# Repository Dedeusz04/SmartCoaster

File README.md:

# Smart Coaster - ESP8266 Beverage Temperature Monitor

An embedded system built on the **NodeMCU ESP8266** that detects cup presence, monitors beverage temperature in real time, and alerts the user when the drink has cooled to a configured target temperature.

## Key Features

- Automatic cup detection (VL6180X ToF sensor)
- Non-contact temperature monitoring (MLX90614 IR sensor) with adaptive liquid temperature estimation
- Configurable brew timer and target drinking temperature
- 128×64 OLED display with rotary encoder menu
- Persistent user settings (EEPROM)
- Audible buzzer alerts
- **Mobile Push Notifications** via [ntfy.sh](https://ntfy.sh) (Max priority alarm)
- **Wi-Fi Connectivity** with network state reporting

For a detailed description, refer to the **project report** included in this repository [v1.Raport_Bartosz.Kępa.pdf](v1.Raport_Bartosz.Kępa.pdf).

## Pin Assignment

| Function | NodeMCU Pin | GPIO |
|---|---|---|
| I2C SDA | D2 | GPIO4 |
| I2C SCL | D1 | GPIO5 |
| Encoder S1 | D5 | GPIO14 |
| Encoder S2 | D6 | GPIO12 |
| Encoder Button | D7 | GPIO13 |
| Buzzer | D0 | GPIO16 |

## Build and Flash

Requires [PlatformIO](https://platformio.org/install/ide). All library dependencies are resolved automatically.

```bash
pio run              # compile
pio run -t upload    # flash to board
pio device monitor   # serial monitor (9600 baud)
```

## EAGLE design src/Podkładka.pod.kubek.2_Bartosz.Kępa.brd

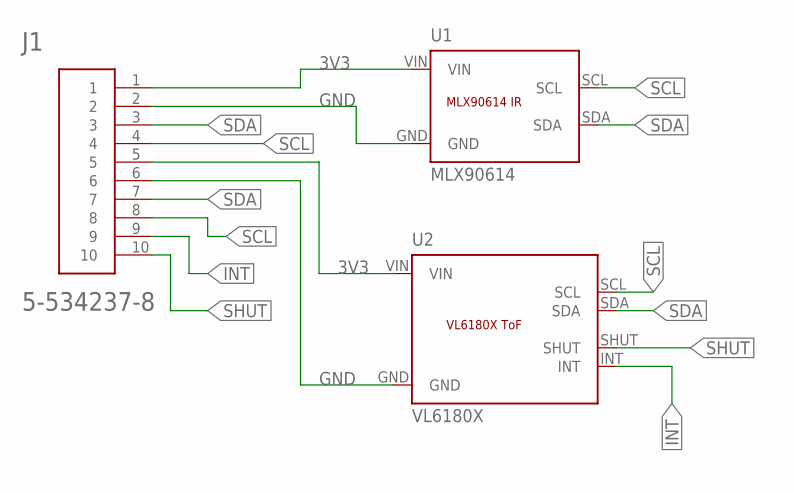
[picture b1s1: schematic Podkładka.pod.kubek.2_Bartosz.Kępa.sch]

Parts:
J1: 5-534237-8
U1: MLX90614; MLX90614_MODULE
U2: VL6180X; VL6180X_MODULE

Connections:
3V3: J1.1, J1.5, U1.VIN, U2.VIN
GND: J1.2, J1.6, U1.GND, U2.GND
INT: J1.9, U2.INT
SCL: J1.4, J1.8, U1.SCL, U2.SCL
SDA: J1.3, J1.7, U1.SDA, U2.SDA
SHUT: J1.10, U2.SHUT

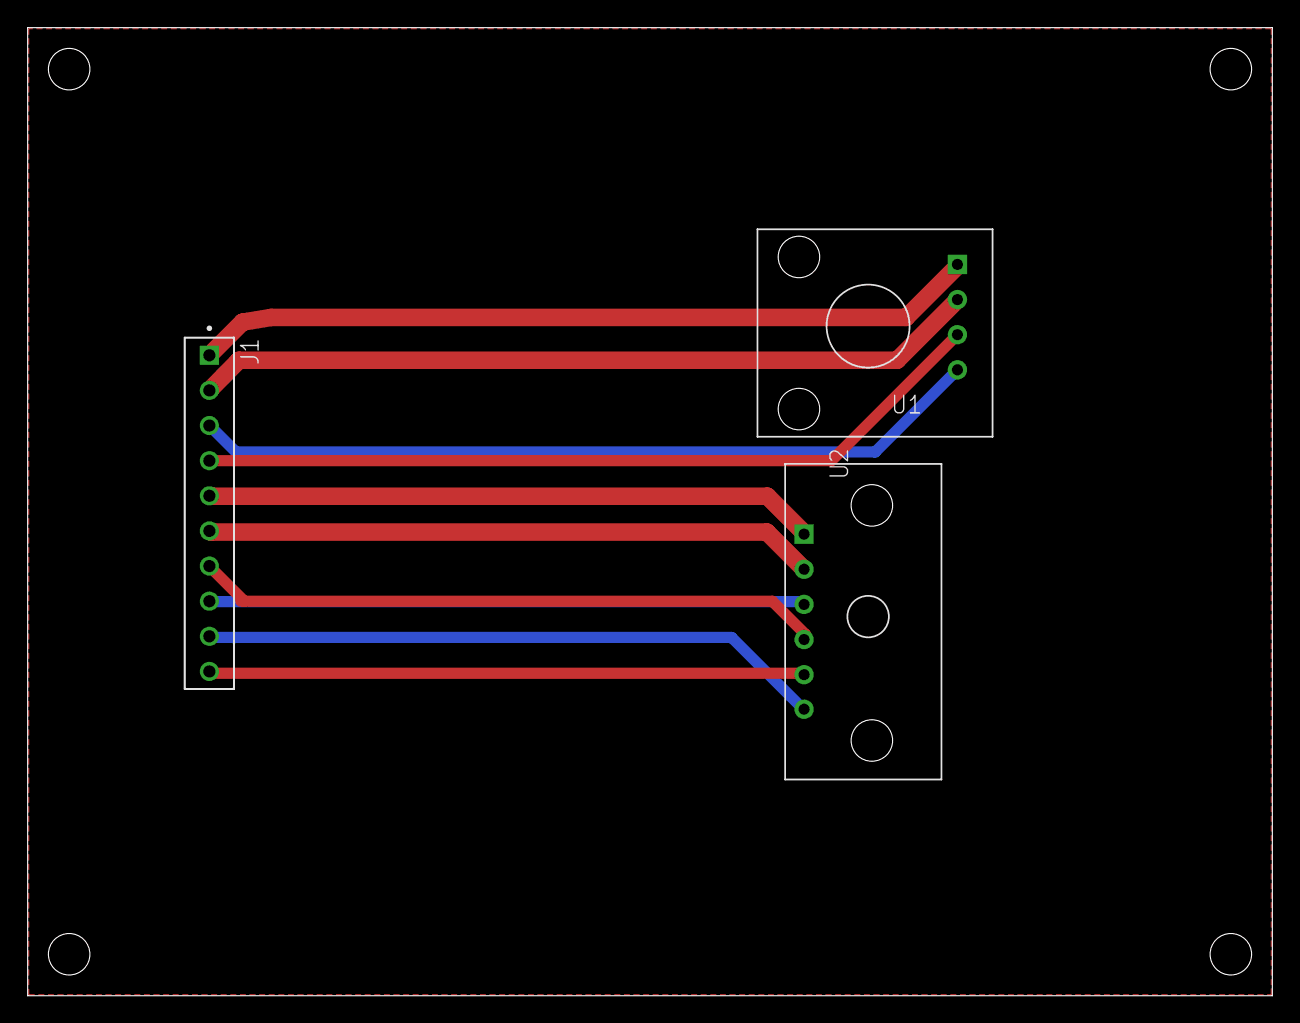
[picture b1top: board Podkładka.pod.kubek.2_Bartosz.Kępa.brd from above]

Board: 2 copper layers, 90.0 x 70.0 mm, 3 parts (0 on the bottom side), 6 nets.

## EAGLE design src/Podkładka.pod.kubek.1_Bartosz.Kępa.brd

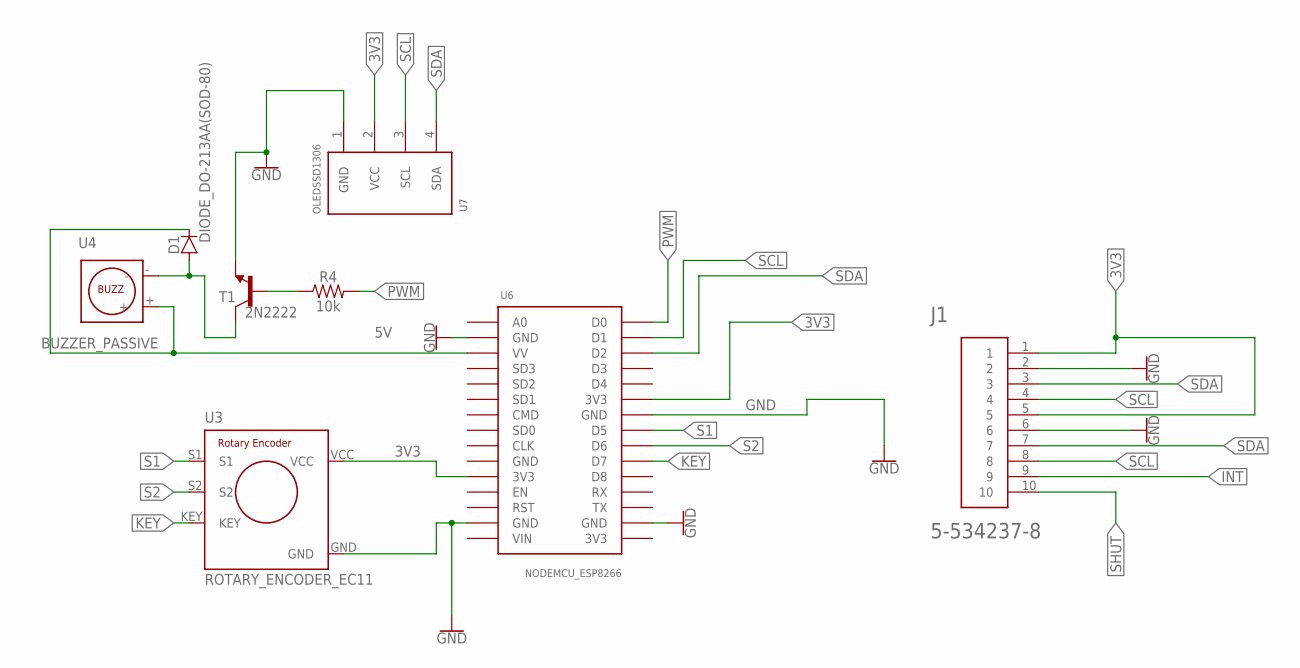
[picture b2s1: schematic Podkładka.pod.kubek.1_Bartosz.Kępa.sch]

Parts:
D1: DIODE_DO-213AA(SOD-80); DIOMELF3516
J1: 5-534237-8
OLEDSSD1306: I2C_OLED; I2C_OLED_PACKAGE
R4: 10k; AXIAL-0.3
T1: 2N2222; TO92-EBC-OVAL
U3: ROTARY_ENCODER_EC11; EC11_ROTARY_ENCODER
U4: BUZZER_PASSIVE; BUZZER_PASSIVE_12MM
U6: NODEMCU_ESP8266

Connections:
3V3: J1.1, J1.5, OLEDSSD1306.2 (VCC), U3.VCC, U6.3V3@1 (3V3), U6.3V3@2 (3V3), U6.3V3@3 (3V3)
5V: D1.1 (C), U4.+, U6.VV
GND: J1.2, J1.6, OLEDSSD1306.1 (GND), T1.E, U3.GND, U6.GND@1 (GND), U6.GND@2 (GND), U6.GND@3 (GND), U6.GND@4 (GND), U6.GND@5 (GND)
INT: J1.9
KEY: U3.KEY, U6.D7
unnamed: R4.P$1 (1), T1.B
unnamed: D1.2 (A), T1.C, U4.-
PWM: R4.P$2 (2), U6.D0
S1: U3.S1, U6.D5
S2: U3.S2, U6.D6
SCL: J1.4, J1.8, OLEDSSD1306.3 (SCL), U6.D1
SDA: J1.3, J1.7, OLEDSSD1306.4 (SDA), U6.D2
SHUT: J1.10
VIN: U6.VIN

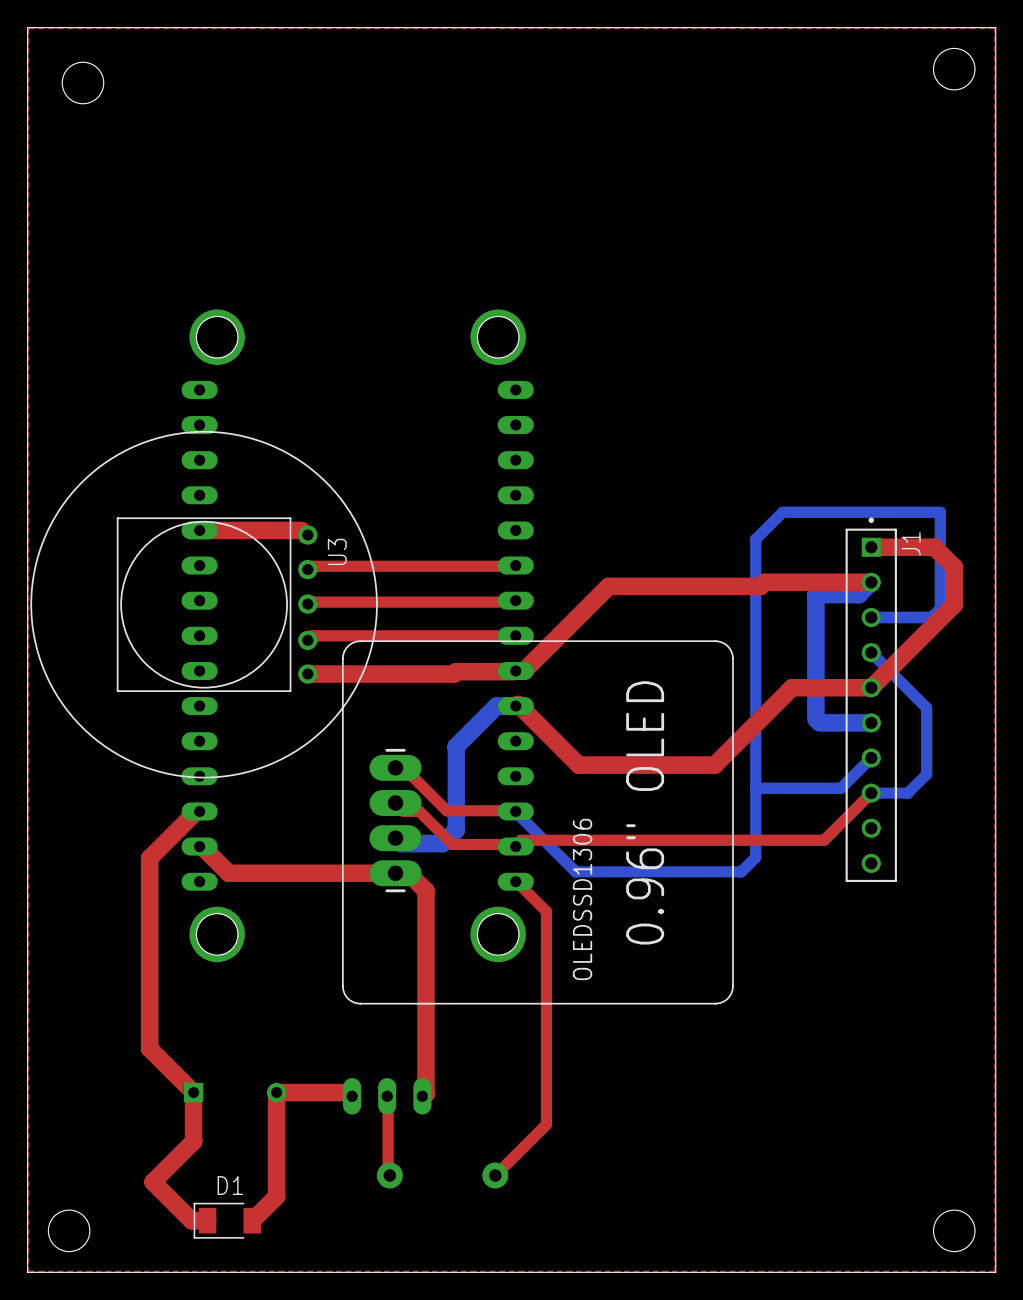
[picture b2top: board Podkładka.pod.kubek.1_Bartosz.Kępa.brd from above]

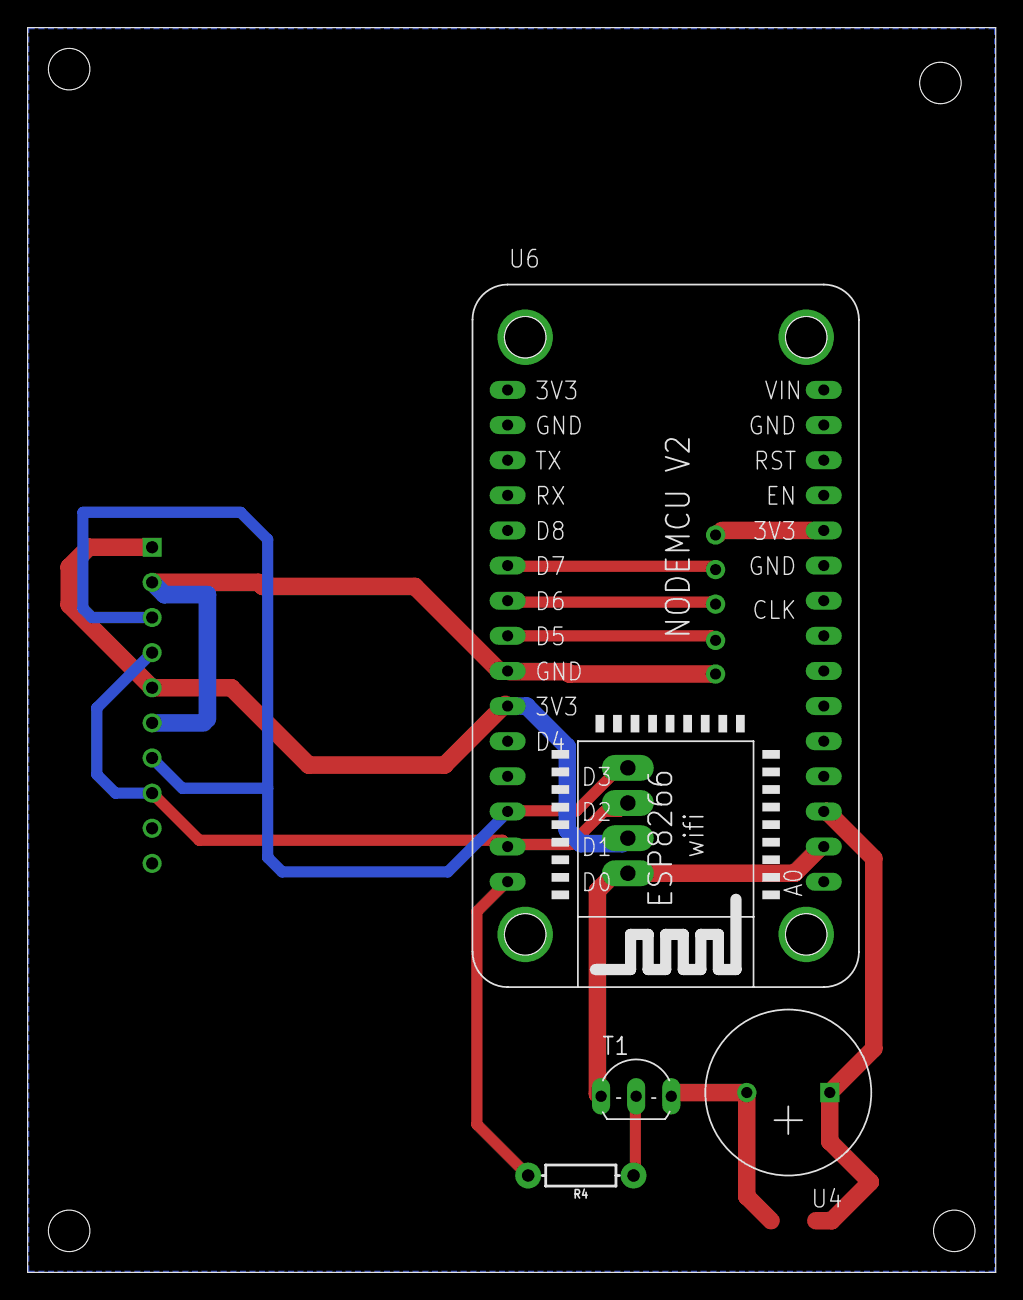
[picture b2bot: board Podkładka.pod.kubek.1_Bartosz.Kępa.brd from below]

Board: 2 copper layers, 70.0 x 90.0 mm, 8 parts (4 on the bottom side), 11 nets.

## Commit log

2026-02-25 Remove license section from README
    Removed license section from README.
2026-04-11 Update code to use Wi-Fi checking and ntfy.sh urgency alarm push notifications
2026-04-11 Add .gitignore and remove .pio from tracking

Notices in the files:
parts and their libraries:
SparkFun-Resistors: Licensing: Creative Commons ShareAlike 4.0 International - https://creativecommons.org/licenses/by-sa/4.0
